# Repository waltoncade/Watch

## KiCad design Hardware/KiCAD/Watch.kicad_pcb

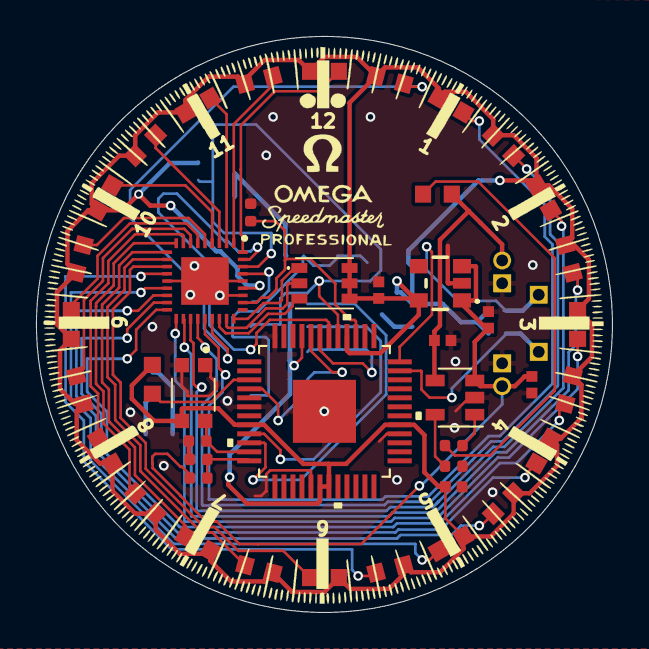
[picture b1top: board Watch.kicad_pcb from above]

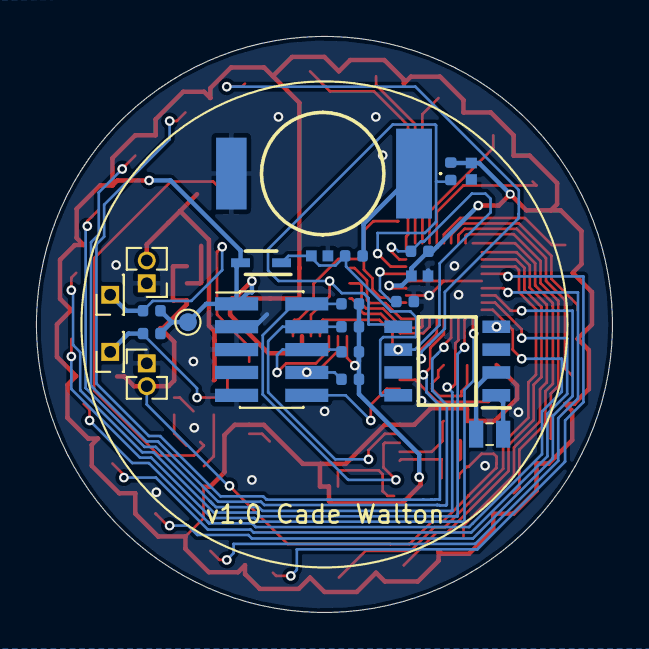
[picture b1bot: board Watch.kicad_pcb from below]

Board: 2 copper layers, 32.0 x 32.0 mm, 66 parts (23 on the bottom side), 52 nets.

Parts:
C101, C102: 4.7uF; CAPC1005X55N
C103, C104, C105, C107, C201: 0.1uF; CAPC1005X55N
C106: RSCSK2043R3D01004T
C202: 1uF; CAPC1005X55N
D101: CUS520,H3F; SOD2513X115N
IC101: TCR2LF33,LM_CT; TCR2LF33LMCT
IC102: PCF85063AT_AY; SOIC127P600X175-8N
IC103: SFH_5711-2_3-Z; SFH571123Z
IC201: IS31FL3235A-QFLS2-TR; QFN40P400X400X80-37N
J101, J105: Conn_01x02; PinHeader_1x02_P1.27mm_Vertical
J102, J103: Conn_01x01; PinHeader_1x01_P1.27mm_Vertical
J104: Conn_ARM_JTAG_SWD_10; PinHeader_2x05_P1.27mm_Vertical_SMD
LED101, LED102, LED201, LED202, LED203, LED204, LED205, LED206, LED207, LED208, LED209, LED210, LED211, LED212, LED213, LED214, LED215, LED216, LED217, LED218, LED219, LED220, LED221, LED222, LED223, LED224: LTST-C191KRKT; LEDC1608X55N
LED225: RGB LED; 150352M173300
R101, R103, R104, R105, R107, R108, R109, R110, R111, R112, R204: 10k; R_0402_1005Metric
R102: 470; R_0402_1005Metric
R106: 56k; R_0402_1005Metric
R113: 1Meg; R_0402_1005Metric
R114: 1MEG; R_0402_1005Metric
R203: 3.3k; R_0402_1005Metric
TP103: TestPoint; TestPoint_Pad_D1.0mm
U101: ATSAM4LS2AA-AU
U102: MCP73831-2-OT; SOT-23-5
Y101: CM8V-T1A-32.768kHz-4pF-20PPM-TA-QC_T3; CM8V32768TA020125

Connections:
+3V3: C104.2, C107.2, C201.1, C202.1, D101.2, IC101.5, IC103.3, IC201.31, J104.1, LED102.2, LED201.2, LED202.2, LED203.2, LED204.2, LED205.2, LED206.2, LED207.2, LED208.2, LED209.2, LED210.2, LED211.2, LED212.2, LED213.2, LED214.2, LED215.2, LED216.2, LED217.2, LED218.2, LED219.2, LED220.2, LED221.2, LED222.2, LED223.2, LED224.2, LED225.2, LED225.4, LED225.6, R103.1, R104.1, R107.1, R108.1, R109.1, R110.1, R111.1, R112.1, TP103.1, U101.8, U101.18, U101.19, U101.29, U101.40, U101.45
+5V: C101.2, J105.2, LED101.2, U102.4
+BATT: C102.2, C103.2, IC101.1, IC101.3, J101.2, R113.2, U102.3
/BattSns: R113.1, R114.2, U101.12
/JTAG_RESET: J104.10, U101.4
/JTAG_TCK: J104.4, R109.2, U101.9
/JTAG_TDI: J104.8, R112.2, U101.44
/JTAG_TDO: J104.6, R111.2, U101.43
/JTAG_TMS: J104.2, R110.2, U101.10
/LED_STAT: LED102.1, U101.3
/SCL: IC102.6, IC201.35, R104.2, U101.42
/SDA: IC102.5, IC201.34, R103.2, U101.41
/SDB: IC201.29, R204.1, U101.39
/SW1: J103.1, R108.2, U101.36
/SW2: J102.1, R107.2, U101.35
/leds/OUT1: IC201.36, LED224.1
/leds/OUT2: IC201.1, LED223.1
/leds/OUT3: IC201.2, LED222.1
/leds/OUT4: IC201.3, LED221.1
/leds/OUT5: IC201.4, LED220.1
/leds/OUT6: IC201.5, LED219.1
/leds/OUT7: IC201.6, LED218.1
/leds/OUT8: IC201.7, LED217.1
/leds/OUT9: IC201.8, LED216.1
/leds/OUT10: IC201.9, LED215.1
/leds/OUT11: IC201.10, LED214.1
/leds/OUT12: IC201.11, LED213.1
/leds/OUT13: IC201.12, LED212.1
/leds/OUT14: IC201.13, LED211.1
/leds/OUT15: IC201.15, LED210.1
/leds/OUT16: IC201.16, LED209.1
/leds/OUT17: IC201.17, LED208.1
/leds/OUT18: IC201.18, LED207.1
/leds/OUT19: IC201.19, LED206.1
/leds/OUT20: IC201.20, LED205.1
/leds/OUT21: IC201.21, LED204.1
/leds/OUT22: IC201.22, LED203.1
/leds/OUT23: IC201.23, LED202.1
/leds/OUT24: IC201.24, LED201.1
/leds/OUT25: IC201.25, LED225.5
/leds/OUT26: IC201.26, LED225.3
/leds/OUT27: IC201.27, LED225.1
/vLUX: IC103.4, R106.2, U101.11
GND: C101.1, C102.1, C103.1, C104.1, C105.1, C106.2, C107.1, C201.2, C202.2, IC101.2, IC102.4, IC103.1, IC103.2, IC201.14, IC201.30, IC201.32, IC201.37, J101.1, J104.3, J104.5, J104.9, J105.1, R101.2, R106.1, R114.1, R203.1, R204.2, U101.6, U101.17, U101.28, U101.48, U101.EPAD, U102.2
unnamed: C105.2, D101.1, IC102.8, R105.2
unnamed: C106.1, R105.1
unnamed: IC102.1, Y101.2
unnamed: IC102.2, Y101.1
unnamed: IC201.33, R203.2
unnamed: LED101.1, R102.1
unnamed: R101.1, U102.5
unnamed: R102.2, U102.1

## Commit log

2021-11-15 Initial Commit, Directory Structure
2021-11-16 Firmware Init
2022-05-05 MCU and PCB cutout complete, ring of lights pattern placed
2022-05-12 Light driver schematic layout complete
2022-06-02 Wireless charging init
2022-06-22 LTSpice zener diode tests. Watch HW now has lipo charger IC and RGB LED for status monitoring
2022-07-01 Hardware mounting aligned. Dimensions set.
2022-07-12 Finalizing watch hardware
2023-02-19 Parnis Config
2023-02-19 Omega layout and silkscreen complete!
2023-03-20 Added various necessary circuits such as light sensor, button pads, RTC cleanup.
2023-04-02 First Schematic layout complete
2023-04-03 Layout almost complete, hitting some snags with routing LED driver
2023-04-04 Signals routed. Ground pours in progress
2023-04-08 Layout complete, pending inspection and purchase
2023-04-16 Release v1.0
2023-11-11 Light flashing!
2023-12-01 Some reason broken?
2023-12-01 Light blinking :)
2023-12-01 Cleanup!
2023-12-01 More buildz
2023-12-01 Debug gone
2023-12-01 Gitignore builds
2023-12-01 Ignore for real

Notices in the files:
parts and their libraries:
Copyright 2021 Accelerated Designs. All rights reserved.
